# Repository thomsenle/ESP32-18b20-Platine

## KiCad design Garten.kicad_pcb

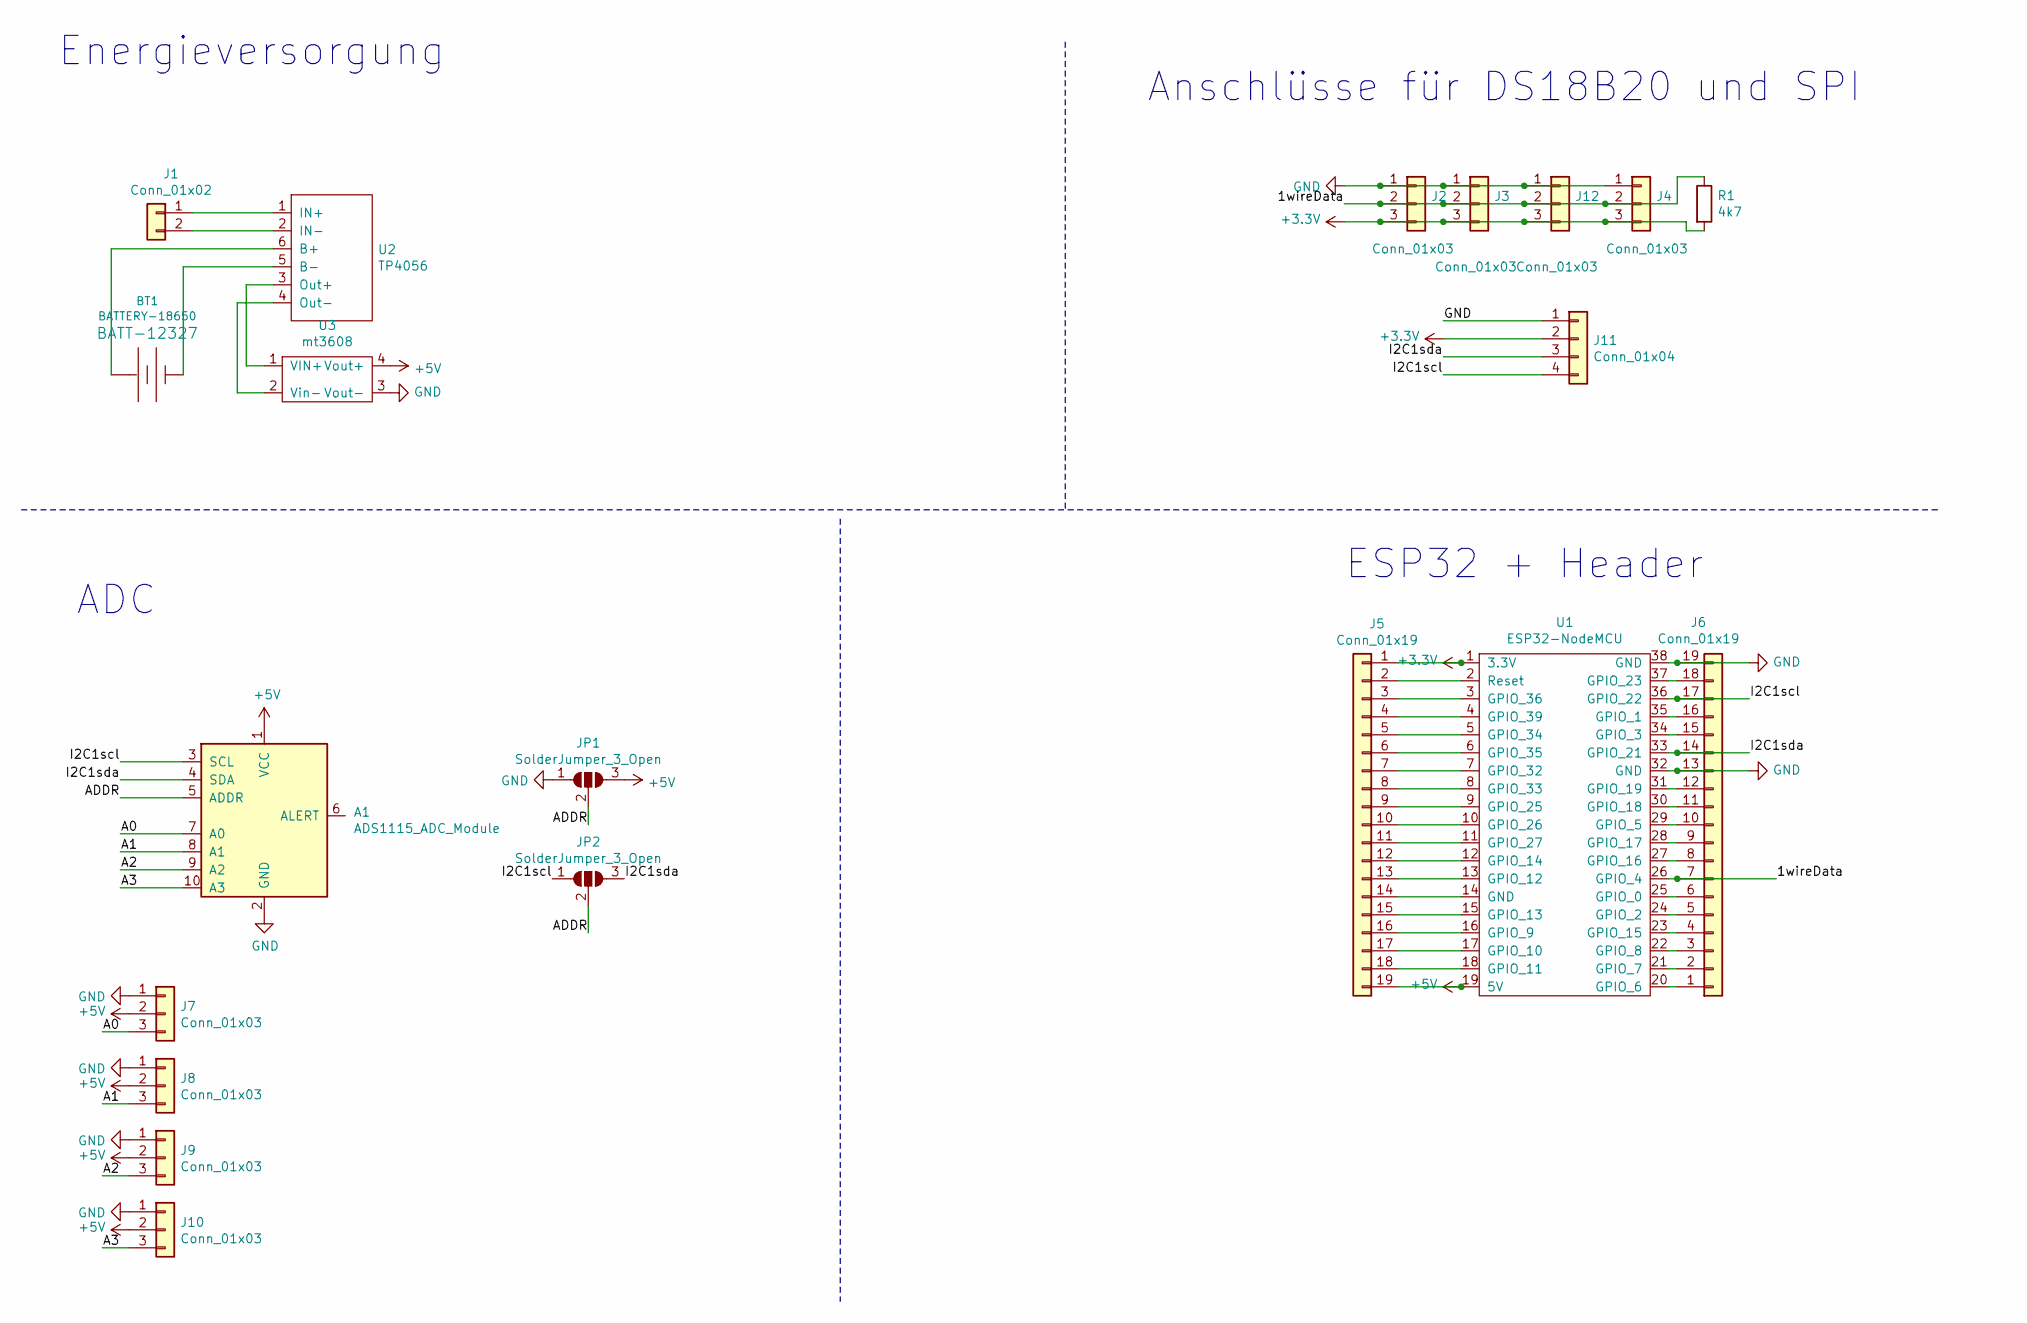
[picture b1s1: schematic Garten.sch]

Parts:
A1: ADS1115_ADC_Module; MODULE_1085
BT1: BATTERY-18650; BatteryHolder_MPD_BH-18650-PC2
J1: Conn_01x02; JST_XH_B2B-XH-A_1x02_P2.50mm_Vertical
J2, J3, J4, J7, J8, J9, J10, J12: Conn_01x03; JST_XH_B3B-XH-A_1x03_P2.50mm_Vertical
J5, J6: Conn_01x19; PinHeader_1x19_P2.54mm_Vertical
J11: Conn_01x04; JST_XH_B4B-XH-A_1x04_P2.50mm_Vertical
JP1, JP2: SolderJumper_3_Open; SolderJumper-3_P1.3mm_Open_Pad1.0x1.5mm
R1: 4k7; R_Axial_DIN0204_L3.6mm_D1.6mm_P7.62mm_Horizontal
U1: ESP32-NodeMCU; DIP-36_906_ELL
U2: TP4056; tp4056
U3: mt3608; MT3608

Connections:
+3V3: J2.3, J3.3, J4.3, J5.1, J11.2, J12.3, R1.2, U1.1 (3.3V)
+5V: A1.1 (VCC), J5.19, J7.2, J8.2, J9.2, J10.2, JP1.3 (B), U1.19 (5V), U3.4 (Vout+)
/1wireData: J2.2, J3.2, J4.2, J6.7, J12.2, R1.1, U1.26 (GPIO_4)
/A0: A1.7 (A0), J7.3
/A1: A1.8 (A1), J8.3
/A2: A1.9 (A2), J9.3
/A3: A1.10 (A3), J10.3
/ADDR: A1.5 (ADDR), JP1.2 (C), JP2.2 (C)
/I2C1scl: A1.3 (SCL), J6.17, J11.4, JP2.1 (A), U1.36 (GPIO_22)
/I2C1sda: A1.4 (SDA), J6.14, J11.3, JP2.3 (B), U1.33 (GPIO_21)
GND: A1.2 (GND), J2.1, J3.1, J4.1, J6.13, J6.19, J7.1, J8.1, J9.1, J10.1, J11.1, J12.1, JP1.1 (A), U1.32 (GND), U1.38 (GND), U3.3 (Vout-)
unnamed: BT1.1 (+), U2.6 (B+)
unnamed: BT1.2 (-), U2.5 (B-)
unnamed: J1.1, U2.1 (IN+)
unnamed: J1.2, U2.2 (IN-)
unnamed: J5.2, U1.2 (Reset)
unnamed: J5.3, U1.3 (GPIO_36)
unnamed: J5.4, U1.4 (GPIO_39)
unnamed: J5.5, U1.5 (GPIO_34)
unnamed: J5.6, U1.6 (GPIO_35)
unnamed: J5.7, U1.7 (GPIO_32)
unnamed: J5.8, U1.8 (GPIO_33)
unnamed: J5.9, U1.9 (GPIO_25)
unnamed: J5.10, U1.10 (GPIO_26)
unnamed: J5.11, U1.11 (GPIO_27)
unnamed: J5.12, U1.12 (GPIO_14)
unnamed: J5.13, U1.13 (GPIO_12)
unnamed: J5.14, U1.14 (GND)
unnamed: J5.15, U1.15 (GPIO_13)
unnamed: J5.16, U1.16 (GPIO_9)
unnamed: J5.17, U1.17 (GPIO_10)
unnamed: J5.18, U1.18 (GPIO_11)
unnamed: J6.1, U1.20 (GPIO_6)
unnamed: J6.2, U1.21 (GPIO_7)
unnamed: J6.3, U1.22 (GPIO_8)
unnamed: J6.4, U1.23 (GPIO_15)
unnamed: J6.5, U1.24 (GPIO_2)
unnamed: J6.6, U1.25 (GPIO_0)
unnamed: J6.8, U1.27 (GPIO_16)
unnamed: J6.9, U1.28 (GPIO_17)
unnamed: J6.10, U1.29 (GPIO_5)
unnamed: J6.11, U1.30 (GPIO_18)
unnamed: J6.12, U1.31 (GPIO_19)
unnamed: J6.15, U1.34 (GPIO_3)
unnamed: J6.16, U1.35 (GPIO_1)
unnamed: J6.18, U1.37 (GPIO_23)
unnamed: U2.3 (Out+), U3.1 (VIN+)
unnamed: U2.4 (Out-), U3.2 (Vin-)

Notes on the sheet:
Energieversorgung
ADC
Anschlüsse für DS18B20 und SPI
ESP32 + Header

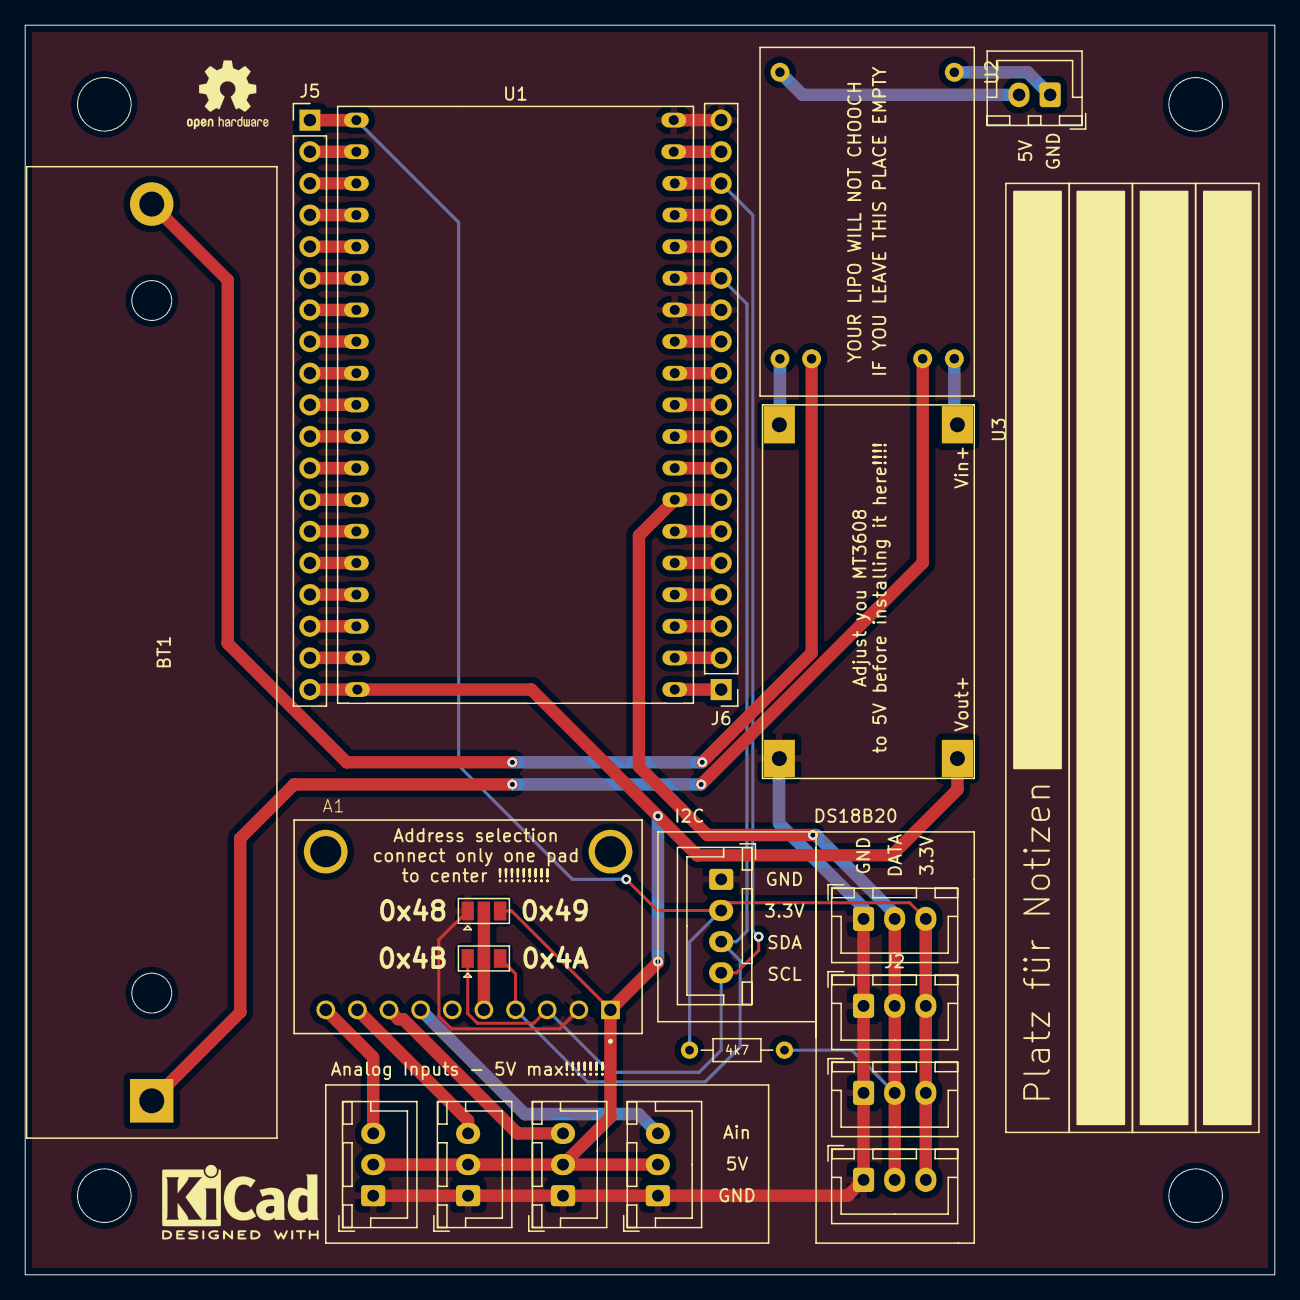
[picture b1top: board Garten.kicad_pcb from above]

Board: 2 copper layers, 100.3 x 100.3 mm, 20 parts (0 on the bottom side), 48 nets.
